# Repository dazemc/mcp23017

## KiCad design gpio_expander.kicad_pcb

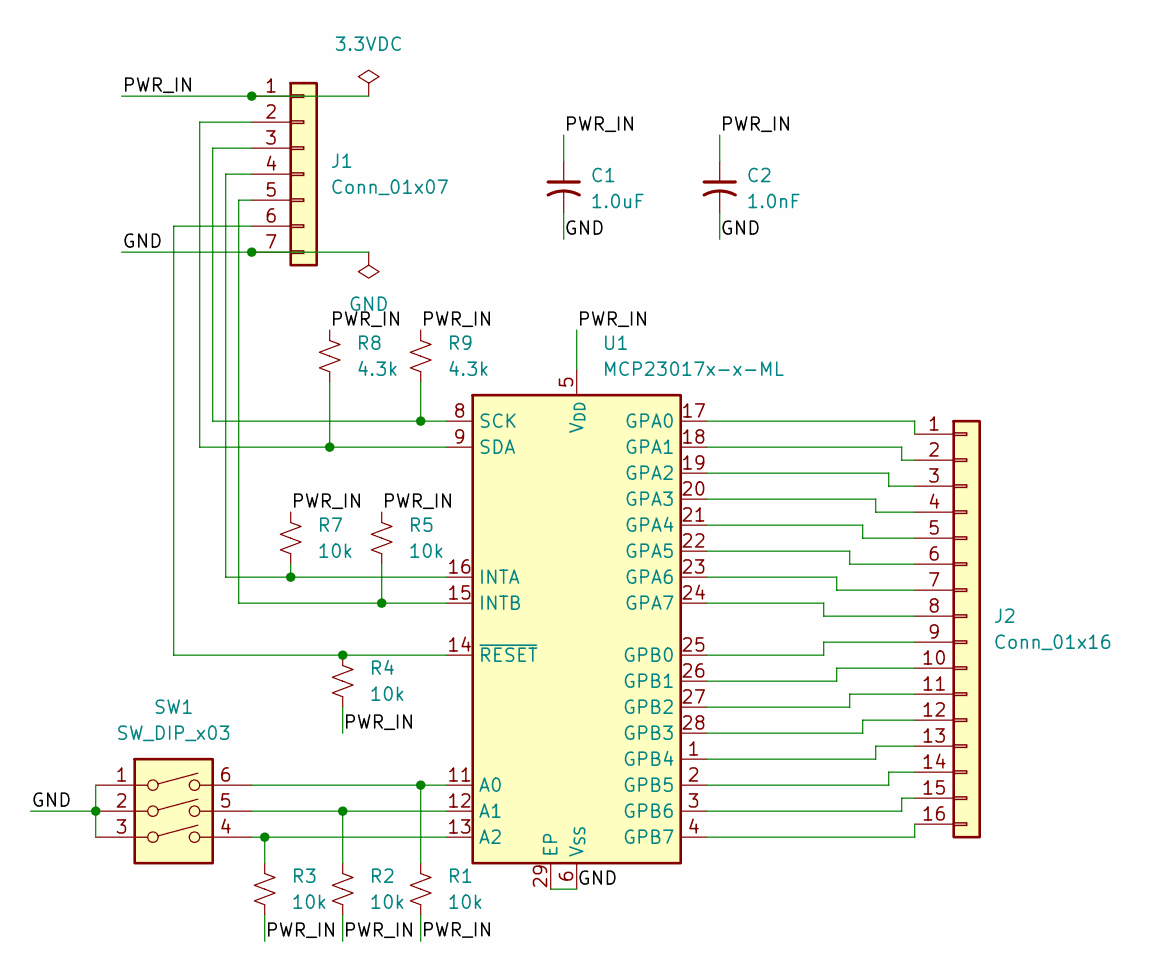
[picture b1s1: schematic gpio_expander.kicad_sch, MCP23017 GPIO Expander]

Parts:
C1: 1.0uF; C_0805_2012Metric_Pad1.18x1.45mm_HandSolder
C2: 1.0nF; C_0805_2012Metric_Pad1.18x1.45mm_HandSolder
J1: Conn_01x07; JST_PH_B7B-PH-K_1x07_P2.00mm_Vertical
J2: Conn_01x16; JST_PH_B16B-PH-K_1x16_P2.00mm_Vertical
R1, R2, R3, R4, R5, R7: 10k; R_0805_2012Metric_Pad1.20x1.40mm_HandSolder
R8, R9: 4.3k; R_0805_2012Metric_Pad1.20x1.40mm_HandSolder
SW1: SW_DIP_x03; 2063ST
U1: MCP23017x-x-ML; QFN-28-1EP_6x6mm_P0.65mm_EP4.25x4.25mm

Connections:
/GND: C1.2, C2.2, J1.7, SW1.1, SW1.2, SW1.3, U1.6 (V_{SS}), U1.29 (EP)
/PWR_IN: C1.1, C2.1, J1.1, R1.2, R2.2, R3.2, R4.1, R5.2, R7.2, R8.2, R9.2, U1.5 (V_{DD})
unnamed: J1.2, R8.1, U1.9 (SDA)
unnamed: J1.3, R9.1, U1.8 (SCK)
unnamed: J1.4, R7.1, U1.16 (INTA)
unnamed: J1.5, R5.1, U1.15 (INTB)
unnamed: J1.6, R4.2, U1.14 (~RESET)
unnamed: J2.1, U1.17 (GPA0)
unnamed: J2.2, U1.18 (GPA1)
unnamed: J2.3, U1.19 (GPA2)
unnamed: J2.4, U1.20 (GPA3)
unnamed: J2.5, U1.21 (GPA4)
unnamed: J2.6, U1.22 (GPA5)
unnamed: J2.7, U1.23 (GPA6)
unnamed: J2.8, U1.24 (GPA7)
unnamed: J2.9, U1.25 (GPB0)
unnamed: J2.10, U1.26 (GPB1)
unnamed: J2.11, U1.27 (GPB2)
unnamed: J2.12, U1.28 (GPB3)
unnamed: J2.13, U1.1 (GPB4)
unnamed: J2.14, U1.2 (GPB5)
unnamed: J2.15, U1.3 (GPB6)
unnamed: J2.16, U1.4 (GPB7)
unnamed: R1.1, SW1.6, U1.11 (A0)
unnamed: R2.1, SW1.5, U1.12 (A1)
unnamed: R3.1, SW1.4, U1.13 (A2)

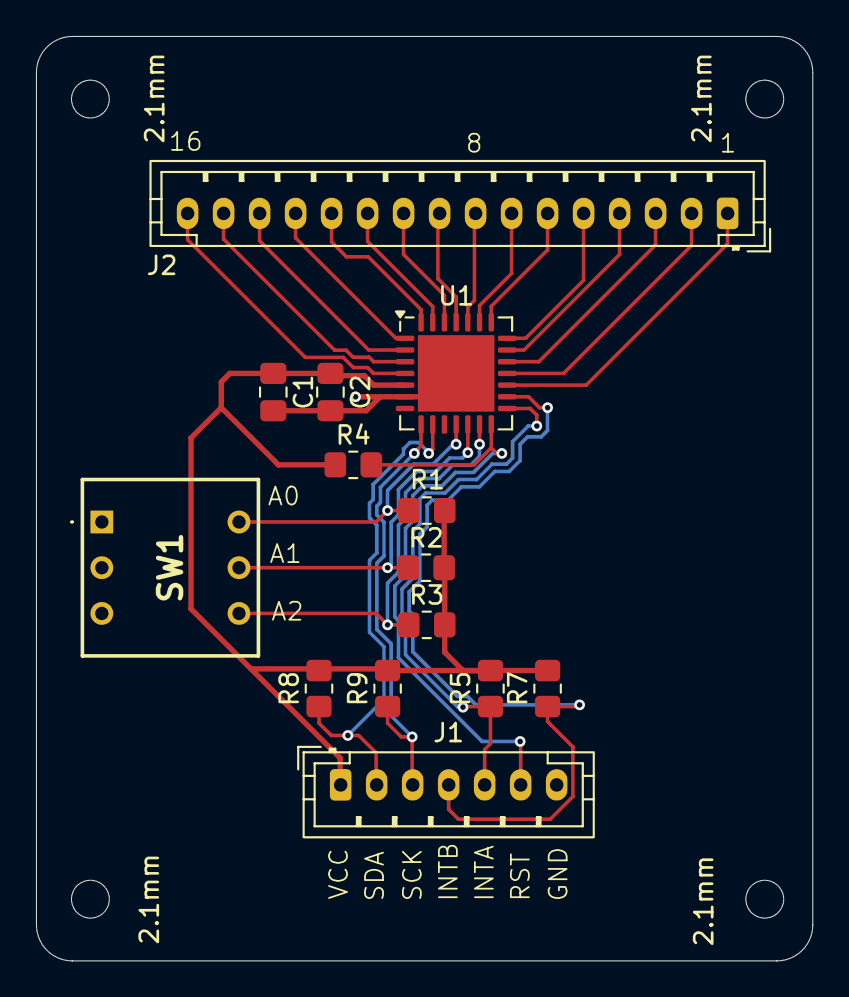
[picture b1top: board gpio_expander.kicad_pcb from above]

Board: 2 copper layers, 43.1 x 51.4 mm, 18 parts (0 on the bottom side), 26 nets.

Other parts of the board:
2.1mm, 2.1mm#2, 2.1mm#3, 2.1mm#4: MountingHole_2.1mm
